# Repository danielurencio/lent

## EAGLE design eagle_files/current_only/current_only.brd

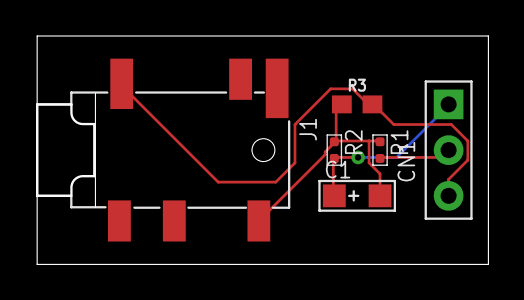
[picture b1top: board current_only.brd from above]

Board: 2 copper layers, 25.0 x 12.6 mm, 6 parts (0 on the bottom side), 4 nets.

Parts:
C1: 10uf; AVX-A
CN1: 3p-2.54; H3-2.54
J1: ST-PJ-312; AUDIO6P-SMD-3.5-14.0X6.4X5.0MM
R1, R2: 10K 1/16W; R0402
R3: 33; 0603

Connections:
+5V: CN1.2, R1.2
GND: C1.+, CN1.1, R2.2
unnamed: C1.-, J1.RS, R1.1, R2.1, R3.1
unnamed: CN1.3, J1.COM2, R3.2

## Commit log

2015-11-16 Second commit
2015-11-16 Third commit
2016-11-01 transformed into a WiFi framework
2016-11-06 client socket
2016-11-19 new client tcp microcontroller
2016-11-21 process
2016-11-21 graph
2016-11-21 path
2016-11-21 paths
2017-01-01 watts

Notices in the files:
parts and their libraries:
SparkFun-Resistors: Licensing: Creative Commons ShareAlike 4.0 International - https://creativecommons.org/licenses/by-sa/4.0
